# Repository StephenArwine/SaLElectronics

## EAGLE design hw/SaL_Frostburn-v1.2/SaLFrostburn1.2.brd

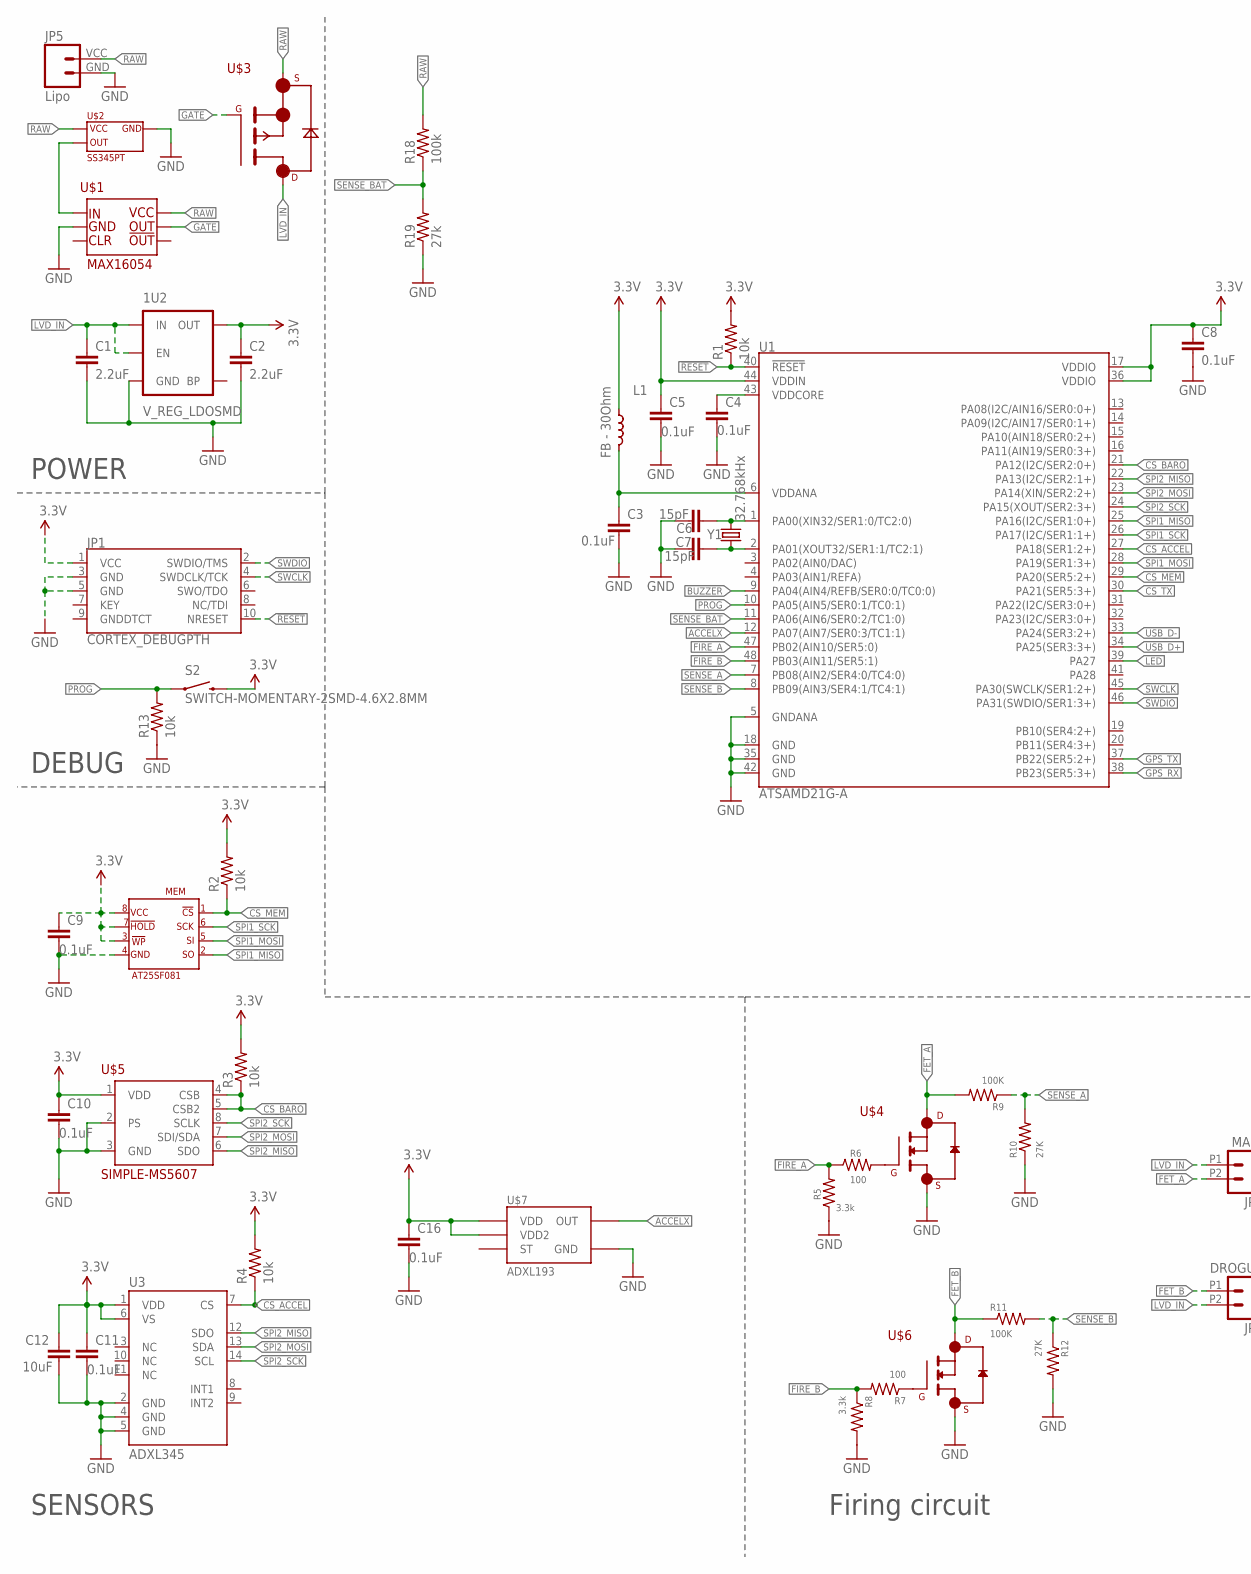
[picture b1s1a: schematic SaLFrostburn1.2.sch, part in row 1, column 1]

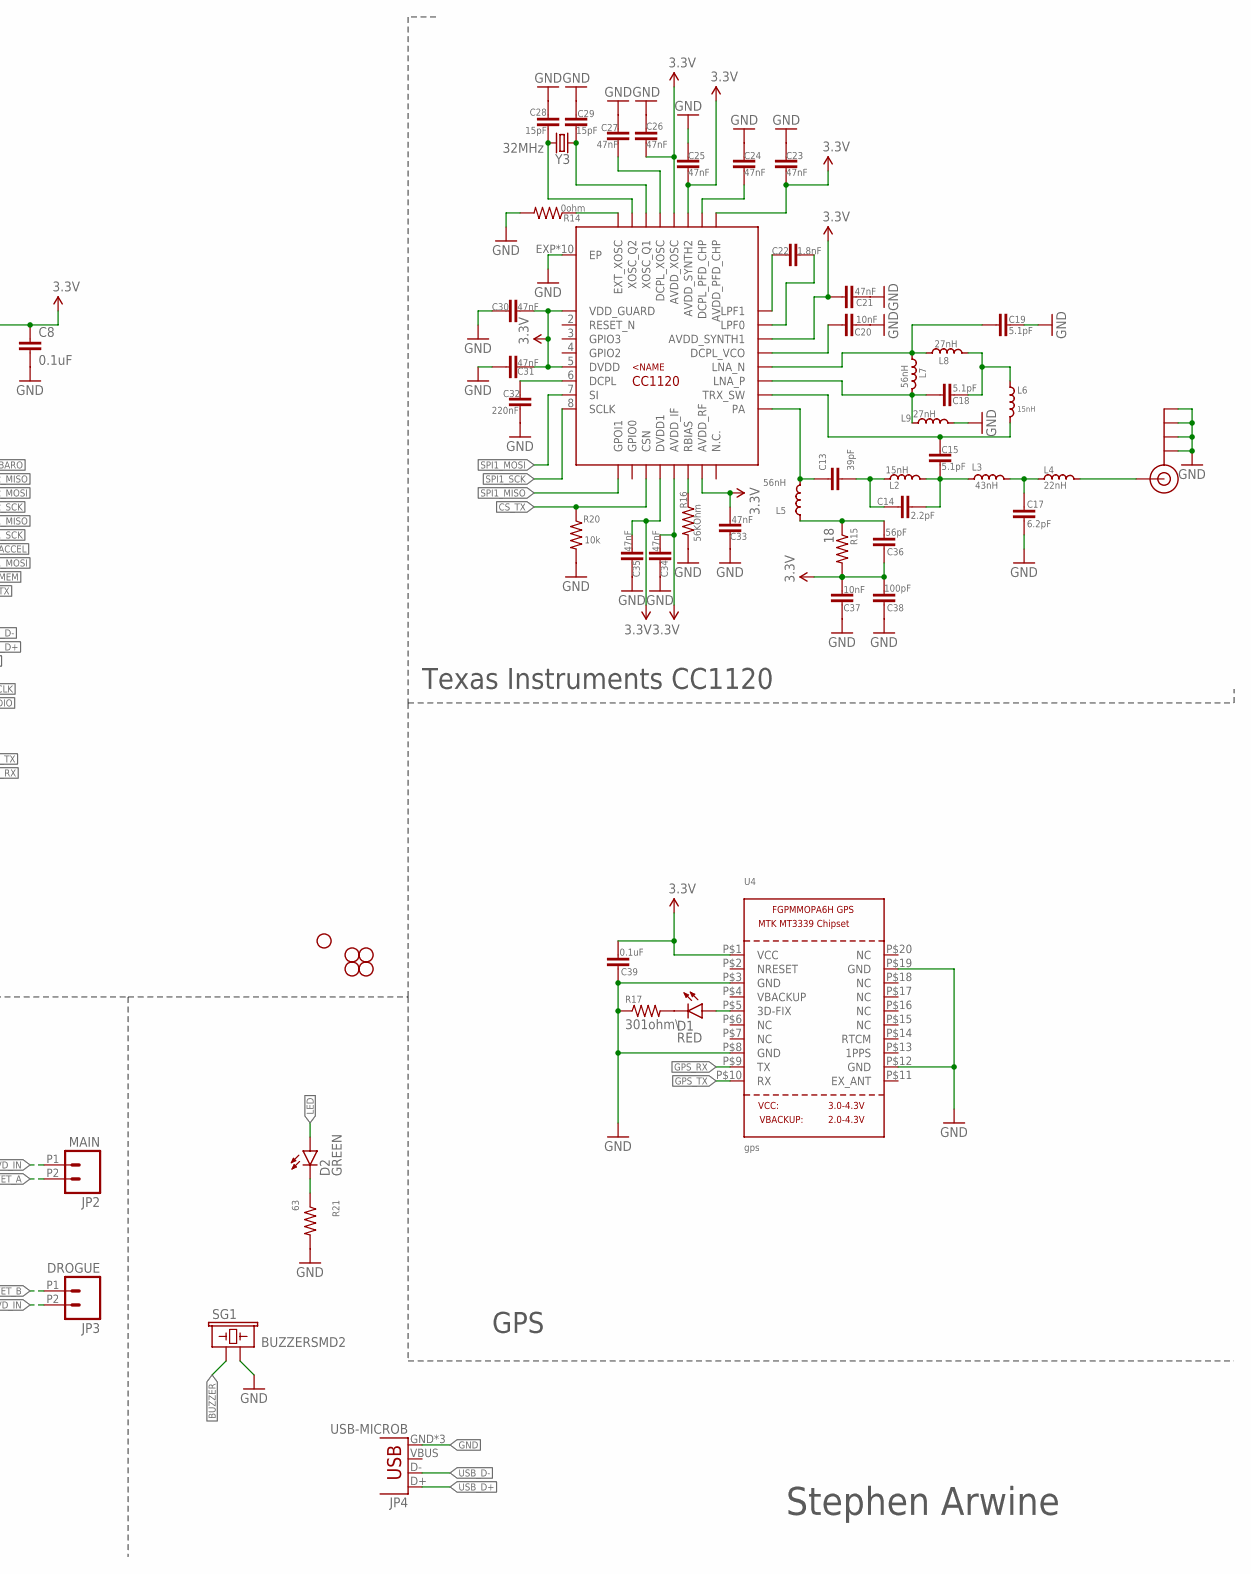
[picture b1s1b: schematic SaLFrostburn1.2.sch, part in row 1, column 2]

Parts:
1U2: V_REG_LDOSMD; SOT23-5
C1, C2: 2.2uF; 0603-CAP
C3, C4, C5, C8, C9, C10, C11, C16, C39: 0.1uF; 0402-CAP
C6, C7, C28, C29: 15pF; 0402-CAP
C12: 10uF; 0402-CAP
C13: 39pF; 0402-CAP
C14: 2.2pF; 0402-CAP
C15, C18, C19: 5.1pF; 0402-CAP
C17: 6.2pF; 0402-CAP
C20, C37: 10nF; 0402-CAP
C21, C23, C24, C25, C26, C27, C30, C31, C33, C34, C35: 47nF; 0402-CAP
C22: 1.8nF; 0402-CAP
C32: 220nF; 0402-CAP
C36: 56pF; 0402-CAP
C38: 100pF; 0402-CAP
D1: RED; LED-0603
D2: GREEN; LED-1206
J$1: SMA_EDGE; SMA-EDGE
JP1: CORTEX_DEBUGPTH; 2X5-PTH-1.27MM
JP2: MAIN; 1X02_2.54_SCREWTERM
JP3: DROGUE; 1X02_2.54_SCREWTERM
JP4: USB-MICROB
JP5: Lipo; JST-2-SMD-VERT
L1: FB - 30Ohm; 0603
L2, L6: 15nH; C0402
L3: 43nH; C0402
L4: 22nH; C0402
L5, L7: 56nH; C0402
L8, L9: 27nH; C0402
MEM: AT25SF081
R1, R2, R3, R4, R13, R20: 10k; 0402-RES
R5, R8: 3.3k; 0402-RES
R6, R7: 100; 0402-RES
R9, R11: 100K; 0402-RES
R10, R12: 27K; 0402-RES
R14: 0ohm; 0402-RES
R15: 18; 0402-RES
R16: 56KOhm; 0402-RES
R17: 301ohm\; 0402-RES
R18: 100k; 0402-RES
R19: 27k; 0402-RES
R21: 63; 0402-RES
S2: SWITCH-MOMENTARY-2SMD-4.6X2.8MM; TACTILE_SWITCH_SMD_4.6X2.8MM
SG1: BUZZERSMD2; BUZZER-CCV
STANDOFF1, STANDOFF2, STANDOFF3, STANDOFF4, STANDOFF5: STAND-OFF
TX/RX: CC1120
U1: ATSAMD21G-A; TQFP-48
U3: ADXL345; LGA14
U4: gps; FGPMMOPA6H
U$1: MAX16054
U$2: SS345PT
U$3: SI7615ADN
U$4, U$6: SIS410DN; POWERPACK1212-8
U$5: SIMPLE-MS5607; MS5607
U$7: ADXL193
Y1: 32.768kHx; CRYSTAL-SMD-3.2X1.5MM
Y3: 32MHz; CRYSTAL-SMD-5X3

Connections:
3.3V: 1U2.5 (OUT), C2.1, C5.1, C8.1, C9.1, C10.1, C11.1, C12.1, C16.1, C21.1, C23.2, C25.2, C26.2, C30.2, C31.2, C33.2, C34.2, C35.2, C36.1, C37.2, C38.2, C39.2, JP1.1 (VCC), L1.1, MEM.!HOLD, MEM.!WP, MEM.VCC, R1.2, R2.2, R3.2, R4.2, R15.2, S2.3 (2), S2.4 (2), TX/RX.1 (VDD_GUARD), TX/RX.5 (DVDD), TX/RX.12 (DVDD1), TX/RX.13 (AVDD_IF), TX/RX.15 (AVDD_RF), TX/RX.22 (AVDD_SYNTH1), TX/RX.25 (AVDD_PFD_CHP), TX/RX.27 (AVDD_SYNTH2), TX/RX.28 (AVDD_XOSC), U1.17 (VDDIO), U1.36 (VDDIO), U1.44 (VDDIN), U3.1 (VDD), U3.6 (VS), U4.P$1 (VCC), U$5.1 (VDD), U$7.P$7 (VDD), U$7.P$8 (VDD2)
!RESET: JP1.10 (NRESET), R1.1, U1.40 (!RESET!)
ACCELX: U1.12 (PA07(AIN7/SER0:3/TC1:1)), U$7.P$6 (OUT)
BUZZER: SG1.+ (1), U1.9 (PA04(AIN4/REFB/SER0:0/TC0:0))
CS_ACCEL: R4.1, U1.27 (PA18(SER1:2+)), U3.7 (CS)
CS_BARO: R3.1, U1.21 (PA12(I2C/SER2:0+)), U$5.4 (CSB), U$5.5 (CSB2)
CS_MEM: MEM.!CS, R2.1, U1.29 (PA20(SER5:2+))
CS_TX: R20.1, TX/RX.11 (CSN), U1.30 (PA21(SER5:3+))
FET_A: JP2.P2 (2), R9.2, U$4.5 (D), U$4.6 (D), U$4.7 (D), U$4.8 (D)
FET_B: JP3.P1 (1), R11.1, U$6.5 (D), U$6.6 (D), U$6.7 (D), U$6.8 (D)
FIRE_A: R5.2, R6.1, U1.47 (PB02(AIN10/SER5:0))
FIRE_B: R7.2, R8.1, U1.48 (PB03(AIN11/SER5:1))
GATE: U$1.OUT, U$3.G
GND: 1U2.2 (GND), C1.2, C2.2, C3.2, C4.2, C5.2, C6.2, C7.2, C8.2, C9.2, C10.2, C11.2, C12.2, C16.2, C17.2, C19.2, C20.2, C21.2, C23.1, C24.1, C25.1, C26.1, C27.1, C28.1, C29.1, C30.1, C31.1, C32.1, C33.1, C34.1, C35.1, C37.1, C38.1, C39.1, J$1.GND@0 (GND), J$1.GND@1 (GND), J$1.GND@2 (GND), J$1.GND@3 (GND), JP1.3 (GND), JP1.5 (GND), JP4.GND, JP4.MT1 (GND), JP4.MT2 (GND), JP5.GND (1), L9.2, MEM.GND, R5.1, R8.2, R10.1, R12.2, R13.1, R14.2, R16.2, R17.1, R19.1, R20.2, R21.2, SG1.- (2), TX/RX.EXP (EP), TX/RX.EXP@1 (EP), TX/RX.EXP@2 (EP), TX/RX.EXP@3 (EP), TX/RX.EXP@4 (EP), TX/RX.EXP@5 (EP), TX/RX.EXP@6 (EP), TX/RX.EXP@7 (EP), TX/RX.EXP@8 (EP), TX/RX.EXP@9 (EP), U1.5 (GNDANA), U1.18 (GND), U1.35 (GND), U1.42 (GND), U3.2 (GND), U3.4 (GND), U3.5 (GND), U4.P$3 (GND), U4.P$8 (GND), U4.P$12 (GND), U4.P$19 (GND), U$1.GND, U$2.GND, U$4.1 (S), U$4.2 (S), U$4.3 (S), U$5.2 (PS), U$5.3 (GND), U$6.1 (S), U$6.2 (S), U$6.3 (S), U$7.P$3 (GND)
GPS_RX: U1.38 (PB23(SER5:3+)), U4.P$9 (TX)
GPS_TX: U1.37 (PB22(SER5:2+)), U4.P$10 (RX)
LED: D2.A, U1.39 (PA27)
LVD_IN: 1U2.1 (IN), 1U2.3 (EN), C1.1, JP2.P1 (1), JP3.P2 (2), U$3.D1 (D), U$3.D2 (D), U$3.D3 (D), U$3.D4 (D)
unnamed: R6.2, U$4.4 (G)
unnamed: U$1.IN, U$2.OUT
unnamed: C6.1, U1.1 (PA00(XIN32/SER1:0/TC2:0)), Y1.P$2 (2)
unnamed: C7.1, U1.2 (PA01(XOUT32/SER1:1/TC2:1)), Y1.P$1 (1)
unnamed: C3.1, L1.2, U1.6 (VDDANA)
unnamed: C4.1, U1.43 (VDDCORE)
unnamed: R7.1, U$6.4 (G)
unnamed: C13.1, L5.2, TX/RX.17 (PA)
unnamed: C13.2, C14.1, L2.1
unnamed: C14.2, C15.1, L2.2, L3.1
unnamed: C17.1, L3.2, L4.1
unnamed: J$1.SIG (SIGNAL), L4.2
unnamed: C15.2, L6.2, TX/RX.18 (TRX_SW)
unnamed: C18.1, L7.2, L9.1, TX/RX.19 (LNA_P)
unnamed: C18.2, L6.1, L8.2
unnamed: C19.1, L7.1, L8.1, TX/RX.20 (LNA_N)
unnamed: C22.1, TX/RX.24 (LPF1)
unnamed: C22.2, TX/RX.23 (LPF0)
unnamed: C20.1, TX/RX.21 (DCPL_VCO)
unnamed: C24.2, TX/RX.26 (DCPL_PFD_CHP)
unnamed: R16.1, TX/RX.14 (RBIAS)
unnamed: R14.1, TX/RX.32 (EXT_XOSC)
unnamed: C27.2, TX/RX.29 (DCPL_XOSC)
unnamed: C29.2, TX/RX.30 (XOSC_Q1), Y3.3 (2)
unnamed: C28.2, TX/RX.31 (XOSC_Q2), Y3.1
unnamed: D2.C, R21.1
unnamed: D1.C, R17.2
unnamed: D1.A, U4.P$5 (3D-FIX)
unnamed: C32.2, TX/RX.6 (DCPL)
unnamed: C36.2, L5.1, R15.1
PROG: R13.2, S2.1, S2.2 (1), U1.10 (PA05(AIN5/SER0:1/TC0:1))
RAW: JP5.VCC (2), R18.2, U$1.VCC, U$2.VCC, U$3.S1 (S), U$3.S2 (S), U$3.S3 (S)
SENSE_A: R9.1, R10.2, U1.7 (PB08(AIN2/SER4:0/TC4:0))
SENSE_B: R11.2, R12.1, U1.8 (PB09(AIN3/SER4:1/TC4:1))
SENSE_BAT: R18.1, R19.2, U1.11 (PA06(AIN6/SER0:2/TC1:0))
SPI1_MISO: MEM.SO, TX/RX.9 (GPOI1), U1.25 (PA16(I2C/SER1:0+))
SPI1_MOSI: MEM.SI, TX/RX.7 (SI), U1.28 (PA19(SER1:3+))
SPI1_SCK: MEM.SCK, TX/RX.8 (SCLK), U1.26 (PA17(I2C/SER1:1+))
SPI2_MISO: U1.22 (PA13(I2C/SER2:1+)), U3.12 (SDO), U$5.6 (SDO)
SPI2_MOSI: U1.23 (PA14(XIN/SER2:2+)), U3.13 (SDA), U$5.7 (SDI/SDA)
SPI2_SCK: U1.24 (PA15(XOUT/SER2:3+)), U3.14 (SCL), U$5.8 (SCLK)
SWCLK: JP1.4 (SWDCLK/TCK), U1.45 (PA30(SWCLK/SER1:2+))
SWDIO: JP1.2 (SWDIO/TMS), U1.46 (PA31(SWDIO/SER1:3+))
USB_D+: JP4.D+, U1.34 (PA25(SER3:3+))
USB_D-: JP4.D-, U1.33 (PA24(SER3:2+))

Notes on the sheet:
POWER
DEBUG
SENSORS
Texas Instruments CC1120
Firing circuit
GPS
Stephen Arwine

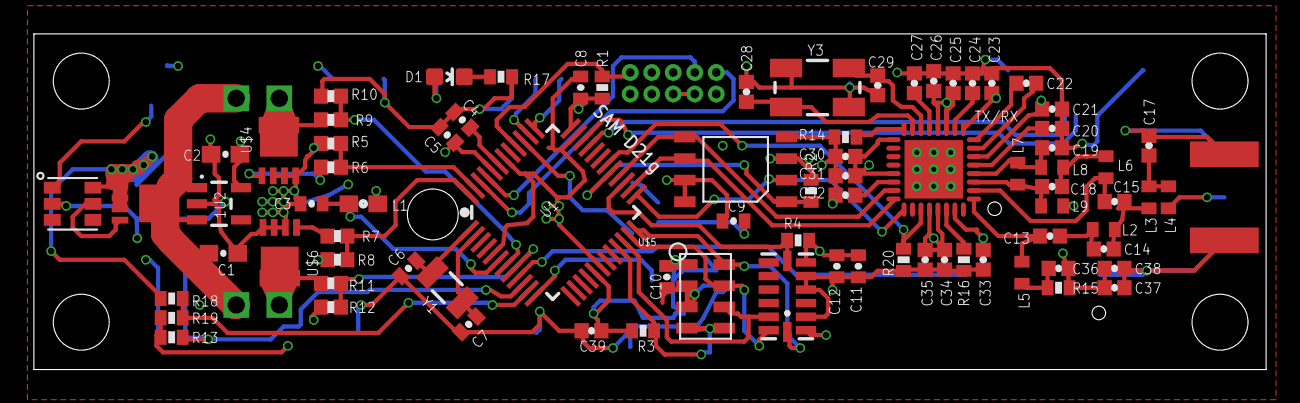
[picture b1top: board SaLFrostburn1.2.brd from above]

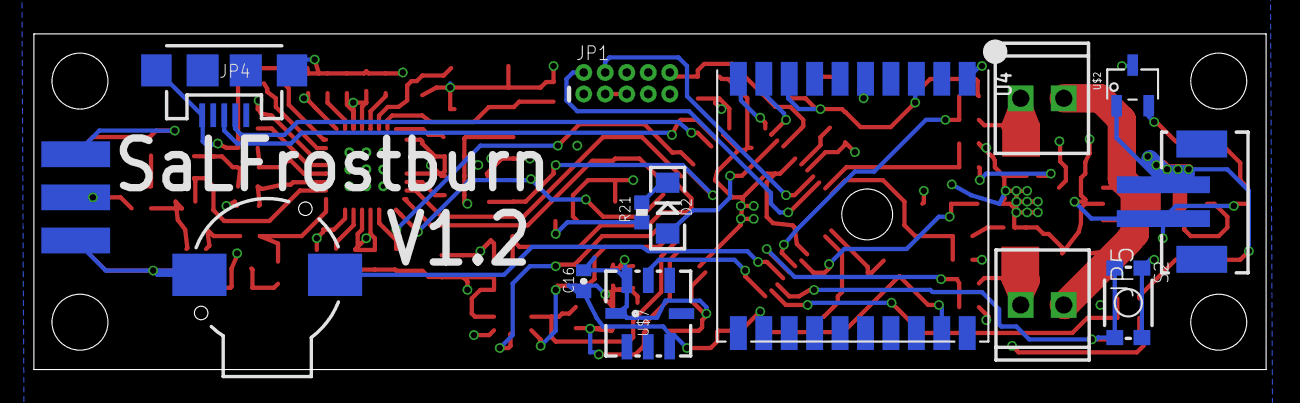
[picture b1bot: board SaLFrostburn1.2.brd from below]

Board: 4 copper layers, 72.7 x 19.8 mm, 99 parts (14 on the bottom side), 63 nets.

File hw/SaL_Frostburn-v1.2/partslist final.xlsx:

Qty | Value | Device | Package | Parts | Description | manufacture | part # | digikey part
11 | 47nF | CAP0402-CAP | 0402-CAP | C21, C23, C24, C25, C26, C27, C30, C31, C33, C34, C35 | Capacitor | Murata | GRM155R71E473KA88D | 490-3254-1-ND
8 | 0.1uF | CAP0402-CAP | 0402-CAP | C3, C4, C5, C8, C9, C10, C11, C39 | Capacitor | Murata | GRM155R61A104KA01D | 490-1318-1-ND
6 | 10k | RESISTOR0402-RES | 0402-RES | R1, R2, R3, R4, R13, R20 | Resistor | Samsung | RC1005F103CS | 1276-3431-1-ND
4 | 15pF | CAP0402-CAP | 0402-CAP | C6, C7, C28, C29 | Capacitor | Murata | GRM1555C1H150JA01D | 490-5888-1-ND
3 | 5.1pF | CAP0402-CAP | 0402-CAP | C15, C18, C19 | Capacitor | Murata | GRM1555C1H5R1CA01D | 490-8216-1-ND
3 | STAND-OFF | STAND-OFF | STAND-OFF | STANDOFF1, STANDOFF2, STANDOFF3 | #4 Stand Off
2 | 10nF | CAP0402-CAP | 0402-CAP | C20, C37 | Capacitor | Murata | GRM155R71E103KA01D | 490-1312-1-ND
2 | 2.2uF | CAP0603-CAP | 0603-CAP | C1, C2 | Capacitor | Samsung | CL10A225KQ8NNNC | 1276-1183-1-ND
2 | 15nH | INDUCTOR0402 | C0402 | L2, L6 | Inductors | Murata | LQW15AN15NJ00D | 490-1148-1-ND
2 | 27nH | INDUCTOR0402 | C0402 | L8, L9 | Inductors | Murata | LQW15AN27NJ00D | 490-1151-1-ND
2 | 56nH | INDUCTOR0402 | C0402 | L5, L7 | Inductors | Murata | LQW15AN56NJ00D | 490-1155-1-ND
2 | 100 | RESISTOR0402 | 0402-RES | R6, R7 | Resistor | Samsung | RC1005F101CS | 1276-3429-1-ND
3 | 100K | RESISTOR0402 | 0402-RES | R9, R11, R18 | Resistor | Samsung | RC1005F104CS | 1276-3432-1-ND
3 | 27K | RESISTOR0402 | 0402-RES | R10, R12, R19 | Resistor | Samsung | RC1005F273CS | 1276-4153-1-ND
2 | 3.3k | RESISTOR0402 | 0402-RES | R5, R8 | Resistor | Samsung | RC1005F332CS | 1276-3460-1-ND
1 | ADXL345 | ADXL345 | LGA14 | U3 | 3-axis SPI/I2C 2/4/8/16g accelerometer | Analog Devices | ADXL345BCCZ-RL | ADXL345BCCZ-RLCT-ND
1 | AT25SF081 | AT25SF081 | AT25SF081 | MEM | AT25SF081 - 8M memory smd | Adesto Technologies | AT25SF081-SSHD-T | 1265-1133-1-ND
1 | ATSAMD21G-A | ATSAMD21G-A | TQFP-48 | U1 | Atmel SAMD21G SMART ARM-Based Microcontroller | Atmel | ATSAMD21G18A-AUT | ATSAMD21G18A-AUTCT-ND
1 | BUZZERSMD2 | BUZZERSMD2 | BUZZER-CCV | SG1 | Buzzer 12mm | CUI Inc. | CBT-09427-SMT-TR | 102-1265-1-ND
1 | 1.8nF | CAP0402-CAP | 0402-CAP | C22 | Capacitor | Murata | GRM1557U1A182JA01D | 490-6274-1-ND
1 | 100pF | CAP0402-CAP | 0402-CAP | C38 | Capacitor | Murata | GRM1555C1H101JA01D | 490-5922-1-ND
1 | 10uF | CAP0402-CAP | 0402-CAP | C12 | Capacitor | Vishay Sprague | 298D106X0004K2T | 718-1615-1-ND
1 | 2.2pF | CAP0402-CAP | 0402-CAP | C14 | Capacitor | Murata | GRM1555C1H2R2CA01D | 490-5932-1-ND
1 | 220nF | CAP0402-CAP | 0402-CAP | C32 | Capacitor | Murata | GRM155R61A224KE19J | 490-6303-1-ND
1 | 39pF | CAP0402-CAP | 0402-CAP | C13 | Capacitor | Murata | GRM1555C1H390JA01D | 490-5871-1-ND
1 | 56pF | CAP0402-CAP | 0402-CAP | C36 | Capacitor | no mount
1 | 6.2pF | CAP0402-CAP | 0402-CAP | C17 | Capacitor | Murata | GRM1555C1H6R2CA01D | 490-11401-1-ND
1 | CC1120 | CC1120 | CC1120 | U2 |  | Texas Instruments | CC1120RHBR | 296-35667-1-ND
1 | CORTEX_DEBUGPTH | CORTEX_DEBUGPTH | 2X5-PTH-1.27MM | JP1 | Cortex Debug Connector | FCI | 20021111-00010T4LF | 609-3712-ND
1 | 32.768kHx | CRYSTAL3.2X1.5MM | CRYSTAL-SMD-3.2X1.5MM | Y1 | Various standard crystals. Proven footprints. | Citizen Finedevice Co Ltd | CM315D32768EZFT | 300-8816-1-ND
1 | 32MHz | CRYSTAL5X3 | CRYSTAL-SMD-5X3 | Y3 | Various standard crystals. Proven footprints. | TXC CORPORATION | 7B-32.000MEEQ-T | 887-1312-1-ND
1 | FRAME-LEDGER | FRAME-LEDGER | CREATIVE_COMMONS | FRAME1 | Schematic Frame
1 | gps | GPS_FGPMMOPA6H | FGPMMOPA6H | U4 | GPS Module - MTK MT3339 Chipset, -165dBm sensitivity, 22 channels, 10Hz, auto-s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
1 | 22nH | INDUCTOR0402 | C0402 | L4 | Inductors | Murata | LQW15AN22NJ00D | 490-1150-1-ND
1 | 43nH | INDUCTOR0402 | C0402 | L3 | Inductors | Murata | LQW15AN43NJ00D | 490-6818-1-ND
1 | FB - 30Ohm | INDUCTOR0603 | 603 | L1 | Inductors | TDK Corporation | MMZ1608Y300BTA00 | 445-2185-1-ND
1 | BAT | JST_2MM_MALE | JST-2-SMD | J1 | Mates to single-cell LiPo batteries. | JST Sales America Inc. | S2B-PH-SM4-TB(LF)(SN) | 455-1749-1-ND
1 | RED | LED-RED0603 | LED-0603 | D1 | Assorted Red LEDs | Rohm Semiconductor |  | 511-1304-1-ND
1 | DROGUE | M022.54MM_SCREWTERM | 1X02_2.54_SCREWTERM | JP3 | Standard 2-pin 0.1 header. Use with"
1 | MAIN | M022.54MM_SCREWTERM | 1X02_2.54_SCREWTERM | JP2 | Standard 2-pin 0.1 header. Use with"
1 | MAX16054 | MAX16054 | MAX16054 | U$1 |  | Maxim Integrated | MAX16054AZT+T | MAX16054AZT+TCT-ND
1 | PTCSMD | PTCSMD | PTC-1206 | F1 | Resettable Fuse PTC | Eaton Bussmann |  | 283-3137-1-ND
1 | 0ohm | RESISTOR0402-RES | 0402-RES | R14 | Resistor | Samsung | RC1005J000CS | 1276-3480-1-ND
1 | 18 | RESISTOR0402-RES | 0402-RES | R15 | Resistor | Samsung | RC1005F180CS | 1276-3893-1-ND
1 | 301ohm | RESISTOR0402-RES | 0402-RES | R17 | Resistor | Samsung | RC1005F3010CS | 1276-3975-1-ND
1 | 56KOhm | RESISTOR0402-RES | 0402-RES | R16 | Resistor | Samsung | RC1005F563CS | 1276-4182-1-ND
1 | SI7232DN | SI7232DN | SI7232DN | U$6 | SI7232DN dual | Vishay Siliconix | SI7232DN-T1-GE3 | SI7232DN-T1-GE3CT-ND
1 | SI7615ADN | SI7615ADN | SI7615ADN | U$3 |  | Vishay Siliconix | SI7615ADN-T1-GE3 | SI7615ADN-T1-GE3CT-ND
1 | SIMPLE-MS5607 | SIMPLE-MS5607 | MS5607 | U$5 |  | TE Connectivity Measurement Specialties | MS560702BA03-50 | 223-1198-1-ND
1 | SMA_EDGE | SMA_EDGE | SMA-EDGE | J$1 | SMA Antenna Connector | Cinch Connectivity Solutions Johnson |  | J502-ND
1 | SS345PT | SS345PT | SS345PT | U$2 |  | Honeywell Sensing and Productivity Solutions | SS345PT | 480-5194-1-ND
1 | SWITCH-MOMENTARY-2SMD-4.6X2.8MM | SWITCH-MOMENTARY-2SMD-4.6X2.8MM | TACTILE_SWITCH_SMD_4.6X2.8MM | S2 | Various NO switches- pushbuttons, reed, etc | C&K Components |  | CKN10284CT-ND
1 | USB-MICROB | USB-MICROB | USB-MICROB | JP4 | USB Connectors |  |  | PRT-08533 ROHS
1 | V_REG_LDOSMD | V_REG_LDOSMD | SOT23-5 | 1U2 | Voltage Regulator LDO | Texas Instruments | TPS73633MDBVREP | 296-21283-1-ND

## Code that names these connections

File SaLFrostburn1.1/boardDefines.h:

#pragma once

#define HAS_SPI_MODULE 1
#include <samd21g18a.h>
#include <samd21.h>
#include <SaLPort.h>

const static Pin senseBat = { .group = 0, .pin = 6 , .chan = 6};


#define INPUT 0
#define OUTPUT 1
#define OUTSTRONG 3
#define TRUE 1
#define FALSE 0
#define SaLFrostburn1_1 1

#define HAS_FLASHMEM 1
#define HAS_AT25SF 1
#define AT25SF_MOSI_PIN PIN_PA19
#define AT25SF_MISO_PIN PIN_PA16
#define AT25SF_SCK_PIN PIN_PA17
#define AT25SF_SLAVE_SELECT_PIN PIN_PA20

const static Pin AT25SF_SLAVE_SELECT = {.group = 0, .pin = 20 };

#define HAS_TX 1
#define CC1120_MOSI_PIN PIN_PA19
#define CC1120_MISO_PIN PIN_PA16
#define CC1120_SCK_PIN PIN_PA17
#define CC1120_SLAVE_SELECT_PIN PIN_PA21

const static Pin CC1120_SLAVE_SELECT = {.group = 0, .pin = 21 };
const static Pin CC1120_MOSI = { .group = 0, .pin = 19 };
const static Pin CC1120_MISO = { .group = 0, .pin = 16 };
const static Pin CC1120_SCK = { .group = 0, .pin = 17 };


const static Pin BUZZER = { .group = 0, .pin = 22, .cfg = 0x40 };


#define HAS_MS5607 1
#define MS5607_MOSI_PIN PIN_PA14
#define MS5607_MISO_PIN PIN_PA13
#define MS5607_SCK_PIN PIN_PA15
#define MS5607_SLAVE_SELECT_PIN PIN_PA12
const static Pin MS5607_MOSI = { .group = 0, .pin = 14 };
const static Pin MS5607_MISO = { .group = 0, .pin = 13 };
const static Pin MS5607_SCK = { .group = 0, .pin = 15 };

const static Pin MS5607_SLAVE_SELECT = {.group = 0, .pin = 12 };


#define HAS_ADXL345 1
#define ADXL345_MOSI_PIN PIN_PA14
#define ADXL345_MISO_PIN PIN_PA13
#define ADXL345_SCK_PIN PIN_PA15
#define ADXL345_SLAVE_SELECT_PIN PIN_PA18

const static Pin ADXL345_SLAVE_SELECT = {.group = 0, .pin = 18 };


#define HAS_GPS 1
#define HAS_MTK3329 1
#define MTK3339_TX_PIN PIN_PB22
#define MTK3339_RX_PIN PIN_PB23

#define HAS_ADXL278 1
const static Pin ADXL278_ACCELX = {.group = 0, .pin = 7, .chan = 7 };


#define MY_ADXL345_DATA_RATE ADXL345_DATARATE_1600_HZ
#define MY_ADXL345_RANGE ADXL345_RANGE_2_G | ADXL345_RANGE_FULL_RANGE

#define NVM_DFLL_COARSE_POS    58
#define NVM_DFLL_COARSE_SIZE   6
#define NVM_DFLL_FINE_POS      64
#define NVM_DFLL_FINE_SIZE     10

#define BUZZERPIN PIN_PA22

const static Pin LedPin = {.group = 0, .pin = 27 };

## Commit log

2016-01-18 :neckbeard: Added .gitattributes & .gitignore files
2016-01-18 initial comit
2016-01-19 working on accelerometer crap
2016-01-20 finally fixed clocks and got others working woohoo
2016-01-21 working on accel and gps stuff
2016-01-22 got accelerometer working and working on v1.5 in eagle
2016-01-23 fucking everything up
2016-01-23 still no progress
2016-01-23 fixed acceleration and bit banging using defines instead of spimodule struct
2016-01-24 fixed types and working on timer stuff
2016-01-24 trying to set up example for rtc
2016-01-27 working on gps
2016-01-28 getting usart working
2016-01-28 sercom stuff
2016-01-29 USART is working woohoo!!!!
2016-01-29 cleaned up main function
2016-01-30 GPS is correctly parsing the time and position!
2016-01-30 messing up explorer
2016-01-31 fixed object orrentatedsensors and created sample
2016-01-31 ground height prototype
2016-01-31 made random mestakes
2016-02-01 timer control up and running!
2016-02-01 15hz sample timer set up
2016-02-02 developed proper sampling algorithm, now samples at 1kHz when it was 300hz
2016-02-03 attempting to start filter stuff
2016-02-04 cleaning up extra code
2016-02-07 some work to usb and flash mem basics
2016-02-11 minor changes
2016-02-11 fixed ignore files
2016-02-11 test
2016-02-11 removed compiled stuff
2016-02-12 setting up usbtest
2016-02-12 deleting junk again
2016-02-12 got usb working!!!
2016-02-12 fixing gitignore
2016-02-13 more usb work
2016-02-14 fixed some nested includes
2016-02-14 minor changes to HW
2016-02-14 minor hardware changes, added led and analog accel
2016-02-15 working on frostburn
2016-02-16 SaLFrostburn-v1.1 hw finished and ordered
2016-02-17 small changes to usb drivers
2016-02-18 first pass at analog read functions
2016-02-18 battery sensing done
2016-02-20 working on non blocking buzzer code
2016-02-20 tuning on buzzer
2016-02-22 first pass at frostburn 1.2
2016-02-28 small changes to buzzer
2016-03-01 made sampleTick a boolean function
2016-03-14 added buzzer to 1.2 hw and setup 1.1 in studio
2016-03-14 setting up 1.1, sensors not working atm
2016-03-14 working on 1.1 sw, mem works, baro and tx do not
2016-03-14 troubleshooting baro, still not working
2016-03-20 1.2 hw sent to fab and some work on 1.1 code
2016-03-27 analog accelerometer up and running, 0g offset needs some work
2016-03-28 pretty pictures
2017-08-20 eagle 8 change
2017-09-01 maybe i fixed things? USART working, parsing not.,
2017-10-03 not real changes
2017-10-22 not sure

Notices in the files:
parts and their libraries:
SparkFun-DigitalIC: Licensing: Creative Commons ShareAlike 4.0 International - https://creativecommons.org/licenses/by-sa/4.0
